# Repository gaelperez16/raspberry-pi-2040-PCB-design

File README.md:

# GAEL'S RP2040 Board

## Overview

This repository contains the complete KiCad project, schematic, PCB layout, 3D renders, and images of the final assembled board for **Gael’s custom RP2040 development board**. It includes a USB-B power interface, LIS3DH accelerometer for motion sensing, push buttons, LEDs, and header pins for debugging and expansion. 

Designed to be compact and circular, this board is suitable for embedded applications, including wearable tech and motion-aware devices.

---

## Features

- **Microcontroller:** Raspberry Pi RP2040
- **Accelerometer:** STMicroelectronics LIS3DH (3-axis, I2C)
- **Debug Header:** SWDIO, SWCLK
- **Buttons:** 3 tactile push buttons
- **LEDs:** 4 indicators
- **USB:** USB Micro-B for power and programming
- **Power Supply:** 3.3V regulated via AMS1117
- **Clock:** 12 MHz crystal oscillator
- **Form Factor:** Custom round PCB

---

## Hardware Components

| Component       | Description                                                       | Datasheet / Link |
|----------------|-------------------------------------------------------------------|------------------|
| [RP2040](https://www.raspberrypi.com/documentation/microcontrollers/rp2040.html) | Dual-core ARM Cortex M0+ microcontroller | [PDF Datasheet](https://datasheets.raspberrypi.com/rp2040/rp2040-datasheet.pdf) |
| [LIS3DH](https://www.st.com/en/mems-and-sensors/lis3dh.html)                     | Low-power 3-axis accelerometer             | [PDF Datasheet](https://www.st.com/resource/en/datasheet/lis3dh.pdf) |
| [AMS1117-3.3](https://www.advanced-monolithic.com/pdf/ds1117.pdf)                | 3.3V Linear Voltage Regulator              | [PDF Datasheet]) |
| USB Micro-B Connector | USB interface for power and programming           | [Example Part](https://www.sparkfun.com/products/9966) |
| 12 MHz Crystal Oscillator | Provides clock source for RP2040                    | [Typical Part](https://www.digikey.com/en/products/detail/ecs-inc/ECS-120-12-33A-EN/3083686) |

---

## Project Structure

```bash
📁 rp2040-board/
├── hardware/
│   ├── RP2040.kicad_sch        # KiCad schematic
│   ├── RP2040.kicad_pcb        # KiCad PCB layout
│   ├── gerbers/                # Gerber fabrication files
├── images/
│   ├── 3D_viewer_top_side.jpg
│   ├── 3D_viewer_bottom_side.jpg
│   ├── Front_and_Back_Layout.jpg
│   ├── Fully_soldered.jpg
│   ├── Fully_soldered_back.jpg
├── README.md                   # Project documentation

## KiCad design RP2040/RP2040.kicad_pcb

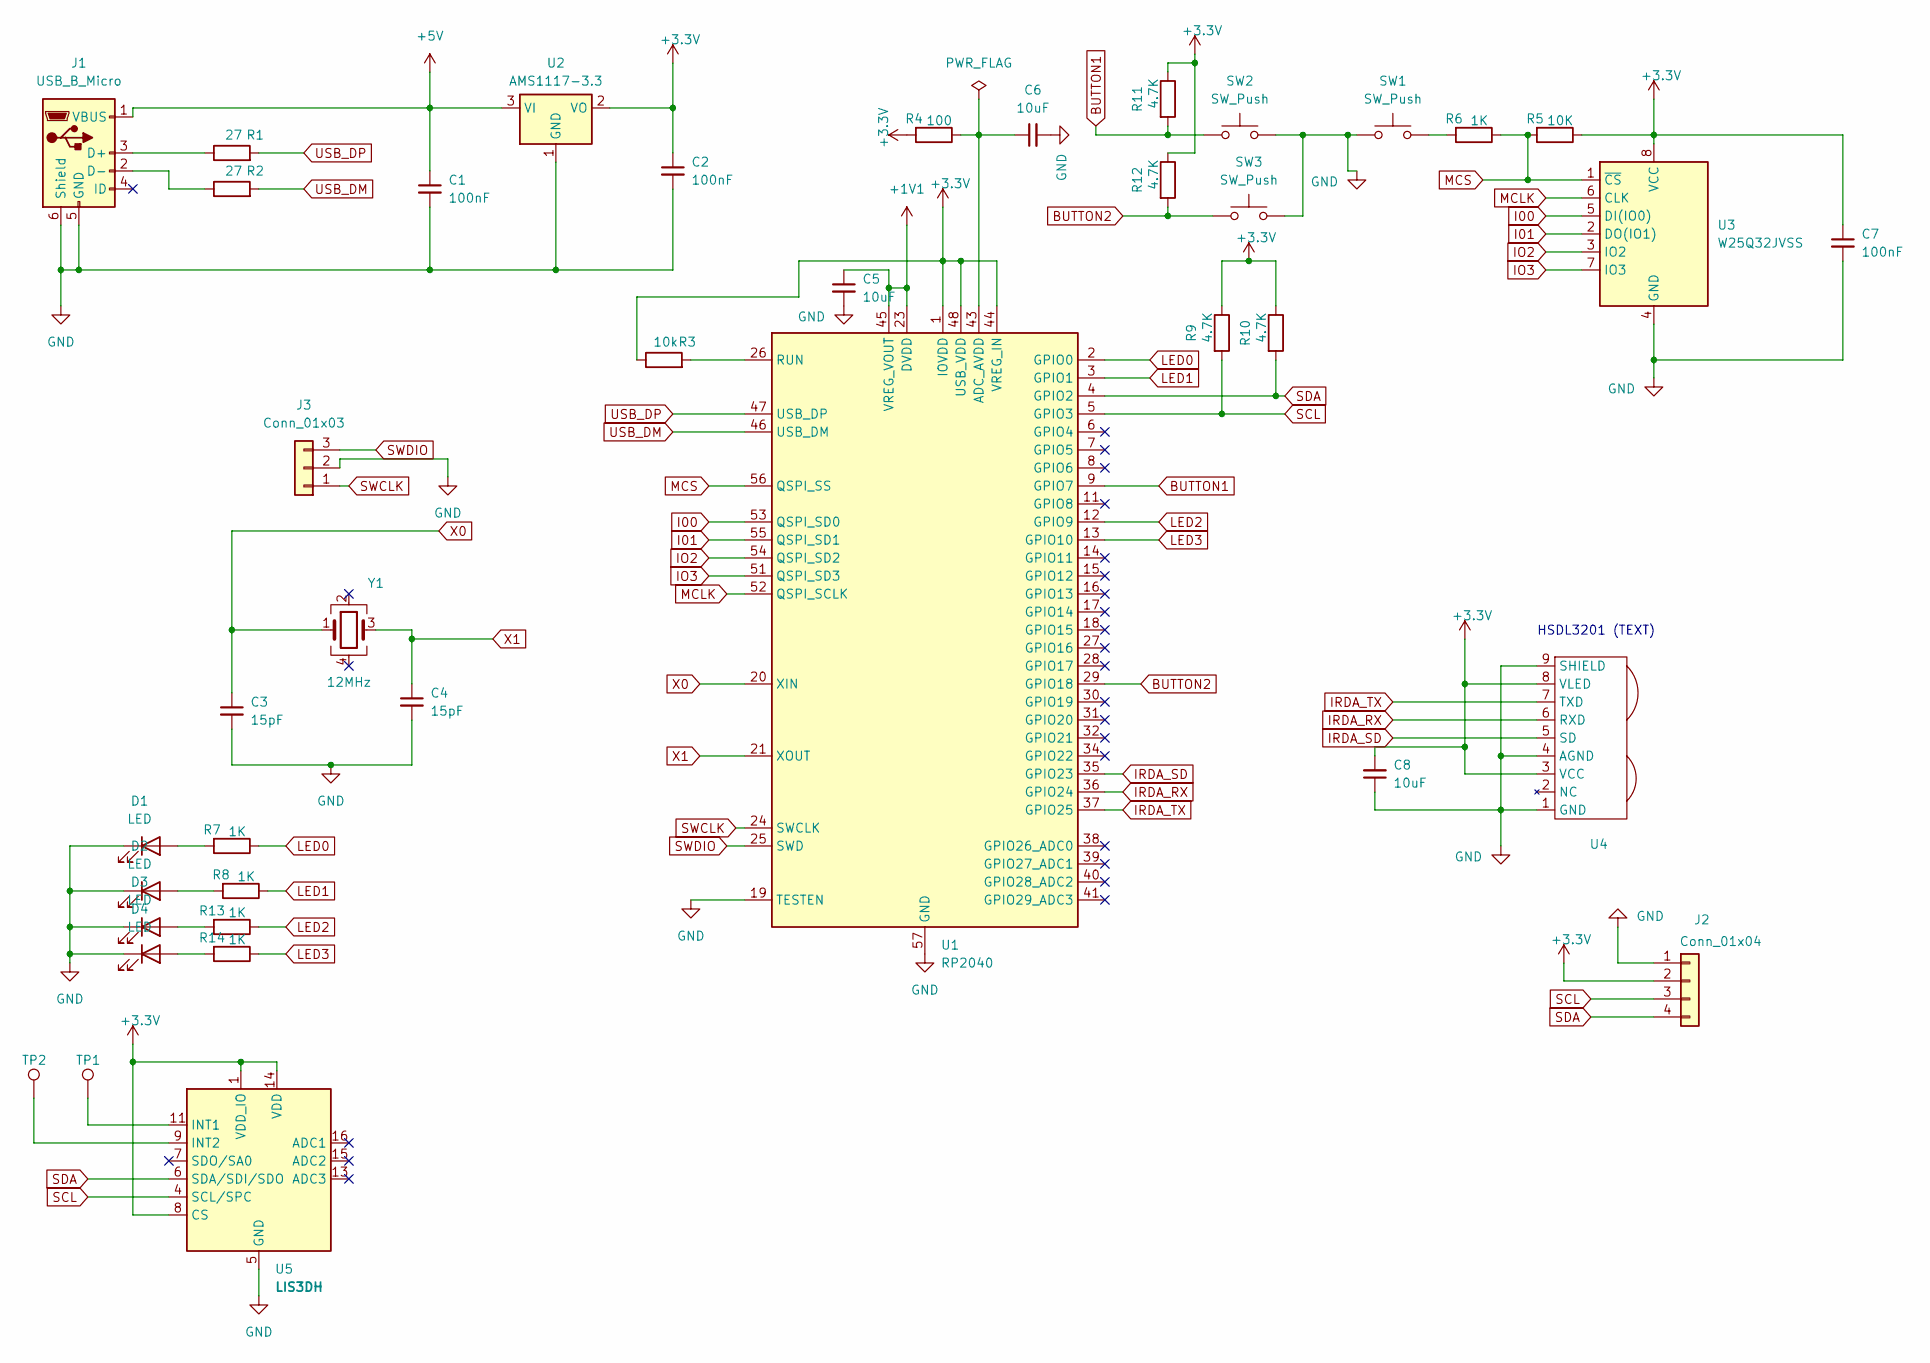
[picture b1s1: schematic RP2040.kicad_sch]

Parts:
C1, C2, C7: 100nF; C_0805_2012Metric
C3, C4: 15pF; C_0805_2012Metric
C5, C6, C8: 10uF; C_0805_2012Metric
D1, D2, D3, D4: LED; LED_0805_2012Metric
J1: USB_B_Micro; USB_Micro-B_Molex_47346-0001
J2: Conn_01x04; PinHeader_1x04_P2.54mm_Vertical
J3: Conn_01x03; PinHeader_1x03_P2.54mm_Vertical
R1, R2: 27; R_0805_2012Metric
R3: 10k; R_0805_2012Metric
R4: 100; R_0805_2012Metric
R5: 10K; R_0805_2012Metric
R6, R7, R8, R13, R14: 1K; R_0805_2012Metric
R9, R10, R11, R12: 4.7K; R_0805_2012Metric
SW1, SW2, SW3: SW_Push; SW_SPST_CK_RS282G05A3
TP1, TP2: TestPoint; TestPoint_Pad_D1.0mm
U1: RP2040; QFN-56-1EP_7x7mm_P0.4mm_EP3.2x3.2mm
U2: AMS1117-3.3; SOT-223-3_TabPin2
U3: W25Q32JVSS; SOIC-8_5.23x5.23mm_P1.27mm
U4: HSDL3201
U5: LIS3DH; LGA-16_3x3mm_P0.5mm_LayoutBorder3x5y
Y1: 12MHz; Crystal_SMD_SeikoEpson_FA238-4Pin_3.2x2.5mm

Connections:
+1V1: C5.1, U1.23 (DVDD), U1.45 (VREG_VOUT), U1.50 (DVDD)
+3.3V: C2.1, C7.1, C8.2, J2.2, R3.1, R4.2, R5.1, R9.1, R10.1, R11.1, R12.1, U1.1 (IOVDD), U1.10 (IOVDD), U1.22 (IOVDD), U1.33 (IOVDD), U1.42 (IOVDD), U1.44 (VREG_IN), U1.48 (USB_VDD), U1.49 (IOVDD), U2.2 (VO), U3.8 (VCC), U4.3 (VCC), U4.8 (VLED), U5.1 (VDD_IO), U5.8 (CS), U5.14 (VDD)
+5V: C1.1, J1.1 (VBUS), U2.3 (VI)
BUTTON1: R11.2, SW2.1, U1.9 (GPIO7)
BUTTON2: R12.2, SW3.1, U1.29 (GPIO18)
GND: C1.2, C2.2, C3.2, C4.2, C5.2, C6.2, C7.2, C8.1, D1.1 (K), D2.1 (K), D3.1 (K), D4.1 (K), J1.5 (GND), J1.6 (Shield), J2.1, J3.2, SW1.1, SW2.2, SW3.2, U1.19 (TESTEN), U1.57 (GND), U2.1 (GND), U3.4 (GND), U4.1 (GND), U4.4 (AGND), U4.9 (SHIELD), U5.5 (GND), U5.10 (GND), U5.12 (GND)
I00: U1.53 (QSPI_SD0), U3.5 (DI(IO0))
I01: U1.55 (QSPI_SD1), U3.2 (DO(IO1))
IO2: U1.54 (QSPI_SD2), U3.3 (IO2)
IO3: U1.51 (QSPI_SD3), U3.7 (IO3)
IRDA_RX: U1.36 (GPIO24), U4.6 (RXD)
IRDA_SD: U1.35 (GPIO23), U4.5 (SD)
IRDA_TX: U1.37 (GPIO25), U4.7 (TXD)
LED0: R7.1, U1.2 (GPIO0)
LED1: R8.1, U1.3 (GPIO1)
LED2: R13.1, U1.12 (GPIO9)
LED3: R14.1, U1.13 (GPIO10)
MCLK: U1.52 (QSPI_SCLK), U3.6 (CLK)
MCS: R5.2, R6.1, U1.56 (QSPI_SS), U3.1 (~CS)
unnamed: D1.2 (A), R7.2
unnamed: D2.2 (A), R8.2
unnamed: D3.2 (A), R13.2
unnamed: D4.2 (A), R14.2
unnamed: J1.3 (D+), R1.1
unnamed: J1.2 (D-), R2.1
unnamed: R6.2, SW1.2
unnamed: C6.1, R4.1, U1.43 (ADC_AVDD)
unnamed: R3.2, U1.26 (RUN)
unnamed: TP1.1, U5.11 (INT1)
unnamed: TP2.1, U5.9 (INT2)
SCL: J2.3, R9.2, U1.5 (GPIO3), U5.4 (SCL/SPC)
SDA: J2.4, R10.2, U1.4 (GPIO2), U5.6 (SDA/SDI/SDO)
SWCLK: J3.1, U1.24 (SWCLK)
SWDIO: J3.3, U1.25 (SWD)
USB_DM: R2.2, U1.46 (USB_DM)
USB_DP: R1.2, U1.47 (USB_DP)
X0: C3.1, U1.20 (XIN), Y1.1
X1: C4.1, U1.21 (XOUT), Y1.3

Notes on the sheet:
HSDL3201 (TEXT)

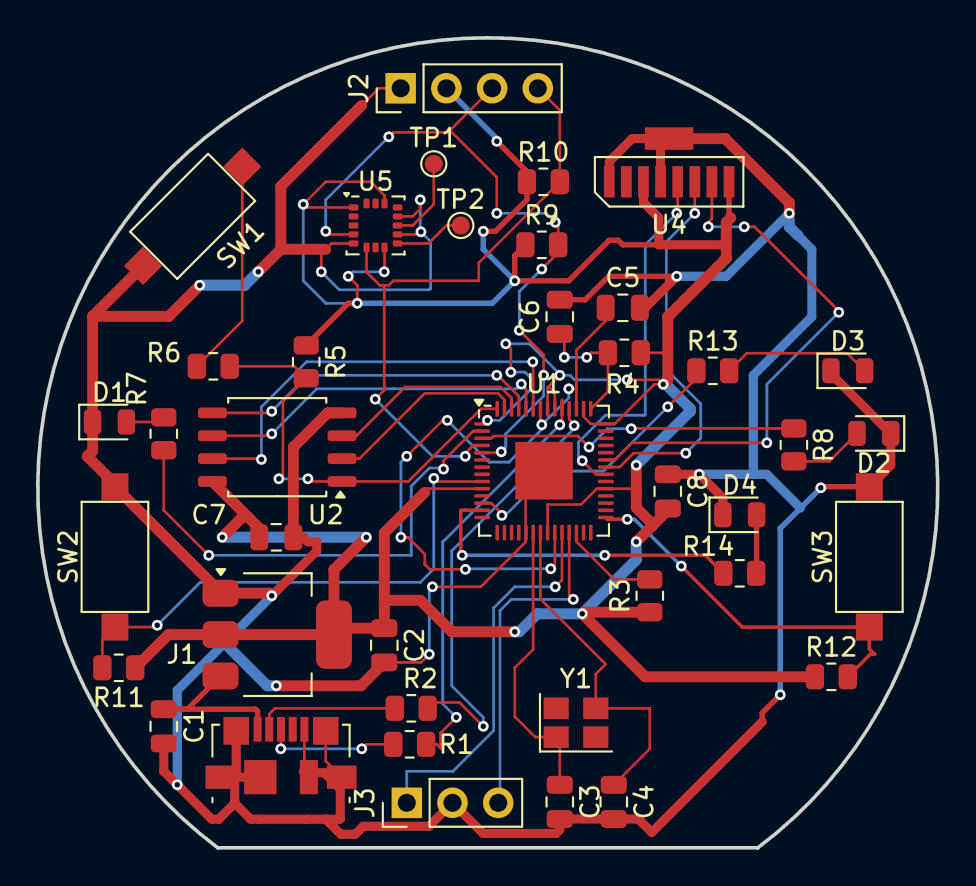
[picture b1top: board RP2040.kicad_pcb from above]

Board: 2 copper layers, 50.0 x 45.0 mm, 40 parts (0 on the bottom side), 38 nets.

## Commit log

2025-05-22 Full Project
2025-05-23 All Files
